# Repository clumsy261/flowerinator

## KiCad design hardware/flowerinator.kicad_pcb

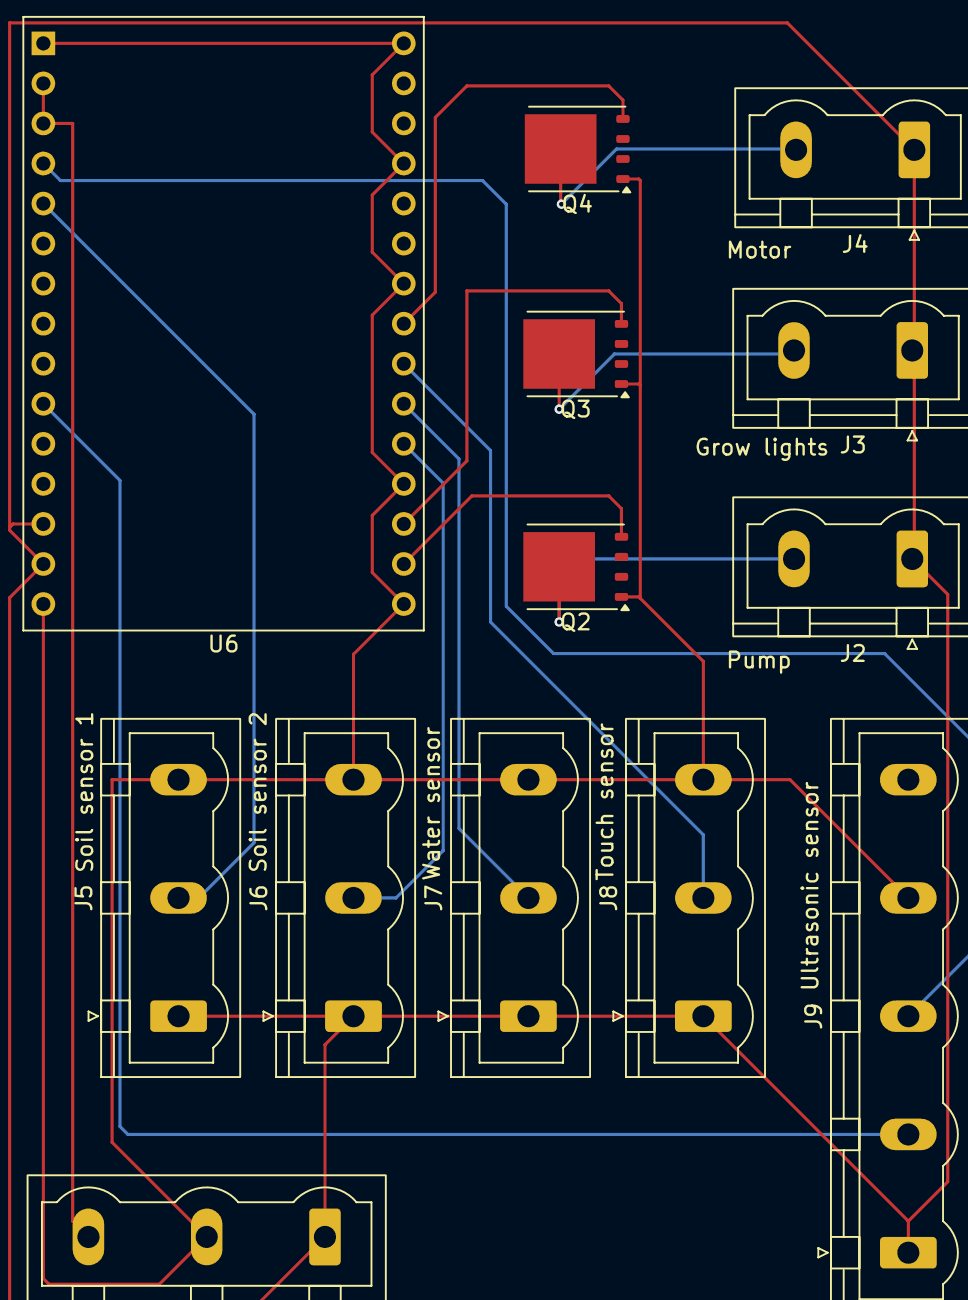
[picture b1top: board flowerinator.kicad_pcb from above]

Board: 2 copper layers, 13 parts (0 on the bottom side), 15 nets.

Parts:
J2, J3, J4: Screw_Terminal_01x02; PhoenixContact_GMSTBVA_2,5_2-G_1x02_P7.50mm_Vertical
J5, J6, J7, J8, J10: Screw_Terminal_01x03; PhoenixContact_GMSTBVA_2,5_3-G_1x03_P7.50mm_Vertical
J9: Screw_Terminal_01x05; PhoenixContact_GMSTBVA_2,5_5-G_1x05_P7.50mm_Vertical
Q2, Q3, Q4: FDMS8350LET40; TDSON-8-1
U6: ESP32-C3-DevKitM-1

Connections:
unnamed: J2.2, Q2.5 (D)
unnamed: J3.2, Q3.5 (D)
unnamed: J4.2, Q4.5 (D)
unnamed: J5.2, U6.5 (IO3)
unnamed: J6.2, U6.20 (IO4)
unnamed: J7.2, U6.21 (IO5)
unnamed: J8.2, U6.22 (IO6)
unnamed: J9.2, U6.10 (IO1)
unnamed: J9.3, U6.4 (IO2)
unnamed: J2.1, J3.1, J4.1, J5.1, J6.1, J7.1, J8.1, J9.1, J10.1, U6.13 (5V), U6.14 (5V)
unnamed: J5.3, J6.3, J7.3, J8.3, J9.4, J10.2, Q2.1 (S), Q2.2 (S), Q2.3 (S), Q3.1 (S), Q3.2 (S), Q3.3 (S), Q4.1 (S), Q4.2 (S), Q4.3 (S), U6.1 (GND), U6.6 (GND), U6.8 (GND), U6.12 (GND), U6.15 (GND), U6.16 (GND), U6.19 (GND), U6.24 (GND), U6.27 (GND), U6.30 (GND)
unnamed: J10.3, U6.2 (3V3), U6.3 (3V3)
unnamed: Q2.4 (G), U6.17 (IO19)
unnamed: Q3.4 (G), U6.18 (IO18)
unnamed: Q4.4 (G), U6.23 (IO7)

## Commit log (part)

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2026-04-09 first
2026-04-10 added some organised folders
2026-04-10 some tidying up
2026-04-10 first schematic commit
2026-04-12 made the web portal
2026-04-13 added second humidity sensor
2026-04-13 finished the api feature on the site
2026-04-14 deleted rust, going on arduino for easier to understand code
2026-04-15 resolved the dependencies for arduino
2026-04-15 Made some adaptations for the arduino code
2026-04-16 almost finished the arduino code
2026-04-17 almost finished the website
2026-04-20 finished the pcb
2026-04-20 schematic
2026-04-21 documentation
2026-04-21 exported the pcb
2026-04-22 more documentation updates
